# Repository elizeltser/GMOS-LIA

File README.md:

# GMOS Testing Setup

This project is the setup code for GMOS testing setup, used for controlling both STM32 evaluation board and ATI to test and sample GMOS gas sensor device using a two-layer lock-in amplifier setup.

## Code Structure

```
GMOS-LIA/
├── src/
│   ├── stm32/          # STM32 evaluation board code
│   ├── ati/            # ATI control module
│   └── lia/            # Lock-in amplifier implementation
├── tests/              # Test suite
├── examples/           # Usage examples
└── README.md
```

## Running Examples

### Prerequisites
- STM32 development environment
- Python 3.8+
- Required dependencies (see requirements.txt)

### Basic Example

```bash
# Install dependencies
pip install -r requirements.txt

# Run example test
python examples/basic_test.py

# Run sensor sampling
python examples/sample_sensor.py
```

### Testing

```bash
# Run all tests
pytest tests/

# Run specific test module
pytest tests/test_lia.py -v
```

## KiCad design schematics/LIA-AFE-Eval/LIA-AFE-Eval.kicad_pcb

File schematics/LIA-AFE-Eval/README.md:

# LIA-AFE-Eval (KiCad project)

Analog front-end evaluation board for the GMOS lock-in readout. It carries only the analog chain (and possibly the bias DACs), is built to be comfortable to use on the lab bench, and is used to debug the analog chain before the production board [LIA-Readout](../LIA-Readout/README.md). The tested circuits are later integrated into LIA-Readout.

| Path | Contents |
|------|----------|
| `LIA-AFE-Eval.kicad_pro`, `*.kicad_sch` | KiCad project and schematic sheets (schematic rev 0.1 entered, layout not started) |
| `../device_libraries/` | Symbol and footprint libraries shared by all boards |
| `docs/` | Design documentation: start with [docs/README.md](docs/README.md) (document map), then `requirements.md` |
| [../tools/](../tools/README.md) | Shared netlist query and check tools; this board's expected results are in [../tools/checks/LIA-AFE-Eval/](../tools/checks/LIA-AFE-Eval/README.md) |
| [../CLAUDE.md](../CLAUDE.md) | Working rules for Claude Code, shared by all schematic projects |

## Sheets

| Page | Sheet name | File | Contents |
|------|------------|------|----------|
| 1 | (root) | `LIA-AFE-Eval.kicad_sch` | Sheet symbols and inter-sheet wiring |
| 2 | Power | `POWER.kicad_sch` | ±15 V (J4) and ±5 V (J5) bench inputs, reverse-polarity diodes, +5VA, −5VA, +5VP through 1 Ω (E-12) |
| 3 | Connectors | `CONNECTORS.kicad_sch` | NUCLEO control header (IF-5), X/Y SMA and header (IF-3), test loops, mounting holes |
| 4 | DAC | `DAC.kicad_sch` | DAC80508 bias DAC (AN-6) |
| 5 | Excitation | `EXCITATION.kicad_sch` | Gate excitation drive |
| 6 | Sensor | `SENSOR.kicad_sch` | GMOS socket, pixel selection, drain bias, drain test loops, heaters |
| 7 | Front_End | `FRONT_END.kicad_sch` | In-amp and band-pass filter |
| 8 | Demod | `DEMODULATOR.kicad_sch` | Synchronous demodulators and post-filters, X and Y channels on one TMUX6136 (E-13) |

The sheets were entered from [docs/requirements.md](docs/requirements.md) rev B and [docs/component_selection.md](docs/component_selection.md) on 2026-10-29 (check file `../tools/checks/LIA-AFE-Eval/T01.txt`). Pins are connected by short wire stubs with labels; inter-sheet signals use hierarchical labels, rails use global power symbols. Shared circuits keep the LIA-Readout designators and net names; new parts start at R58, C52, U23, D9, J7, TP1. Simulations of the front end are in [`simulations/`](../../simulations/README.md).

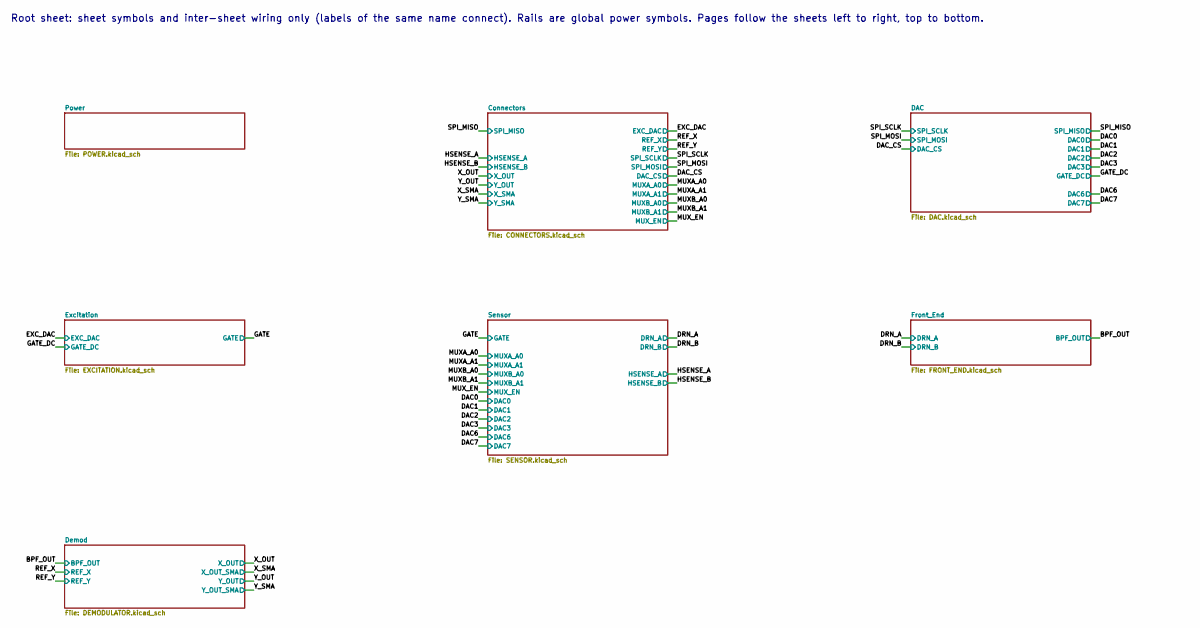
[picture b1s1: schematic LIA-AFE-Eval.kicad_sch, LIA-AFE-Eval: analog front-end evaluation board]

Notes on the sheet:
Root sheet: sheet symbols and inter-sheet wiring only (labels of the same name connect). Rails are global power symbols. Pages follow the sheets left to right, top to bottom.

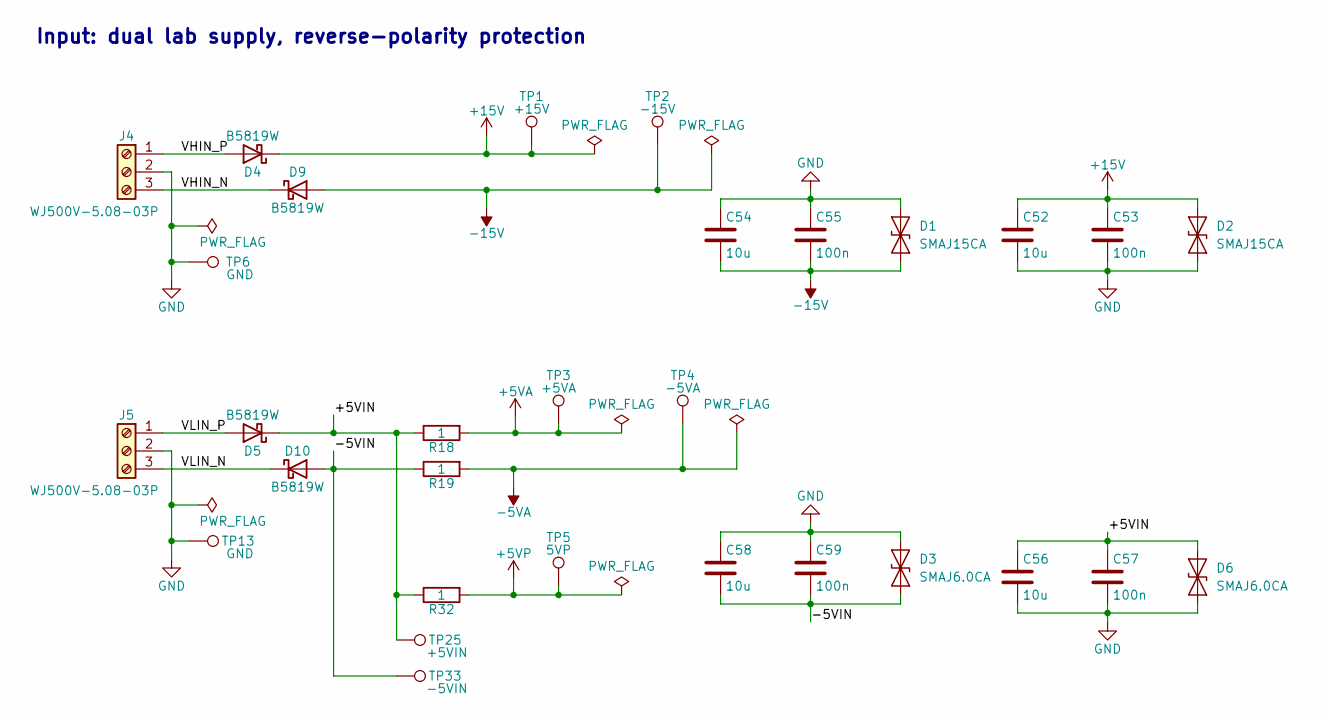
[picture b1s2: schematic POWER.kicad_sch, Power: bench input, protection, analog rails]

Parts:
C52, C54, C56, C58: 10u; C_1206_3216Metric; Voltage 25V
C53, C55, C57, C59: 100n; C_0603_1608Metric
D1, D2: SMAJ15CA; D_SMA
D3, D6: SMAJ6.0CA; D_SMA
D4, D5, D9, D10: B5819W; D_SOD-123; MPN B5819W; LCSC C64885
J4, J5: WJ500V-5.08-03P; TerminalBlock_Phoenix_MKDS-1,5-3-5.08_1x03_P5.08mm_Horizont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; MPN WJ500V-5.08-03P; LCSC C72334
R18, R19, R32: 1; R_0603_1608Metric; Tolerance 0.1%; MPN PTFR0603B1K00N9; LCSC C394536
TP1: +15V; TestPoint_Keystone_5000-5004_Miniature; MPN Keystone 5000; LCSC C5199900
TP2: -15V; TestPoint_Keystone_5000-5004_Miniature; MPN Keystone 5000; LCSC C5199900
TP3: +5VA; TestPoint_Keystone_5000-5004_Miniature; MPN Keystone 5000; LCSC C5199900
TP4: -5VA; TestPoint_Keystone_5000-5004_Miniature; MPN Keystone 5000; LCSC C5199900
TP5: 5VP; TestPoint_Keystone_5000-5004_Miniature; MPN Keystone 5000; LCSC C5199900
TP6, TP13: GND; TestPoint_Keystone_5000-5004_Miniature; MPN Keystone 5001; LCSC C238122
TP25: +5VIN; TestPoint_Keystone_5000-5004_Miniature; MPN Keystone 5001; LCSC C238122
TP33: -5VIN; TestPoint_Keystone_5000-5004_Miniature; MPN Keystone 5001; LCSC C238122

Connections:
+5VA: R18.2, TP3.1 (1_1); also elsewhere on the board
+5VP: R32.2, TP5.1 (1_1); also elsewhere on the board
+15V: C52.1, C53.1, D2.2 (A2), D4.1 (K), TP1.1 (1_1); also elsewhere on the board
-5VA: R19.2, TP4.1 (1_1); also elsewhere on the board
-15V: C54.2, C55.2, D1.1 (A1), D9.2 (A), TP2.1 (1_1); also elsewhere on the board
/Power/+5VIN: C56.1, C57.1, D5.1 (K), D6.2 (A2), R18.1, R32.1, TP25.1 (1_1)
/Power/-5VIN: C58.2, C59.2, D3.1 (A1), D10.2 (A), R19.1, TP33.1 (1_1)
/Power/VHIN_N: D9.1 (K), J4.3
/Power/VHIN_P: D4.2 (A), J4.1
/Power/VLIN_N: D10.1 (K), J5.3
/Power/VLIN_P: D5.2 (A), J5.1
GND: C52.2, C53.2, C54.1, C55.1, C56.2, C57.2, C58.1, C59.1, D1.2 (A2), D2.1 (A1), D3.2 (A2), D6.1 (A1), J4.2, J5.2, TP6.1, TP13.1 (1_1); also elsewhere on the board

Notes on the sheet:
Input: dual lab supply, reverse-polarity protection

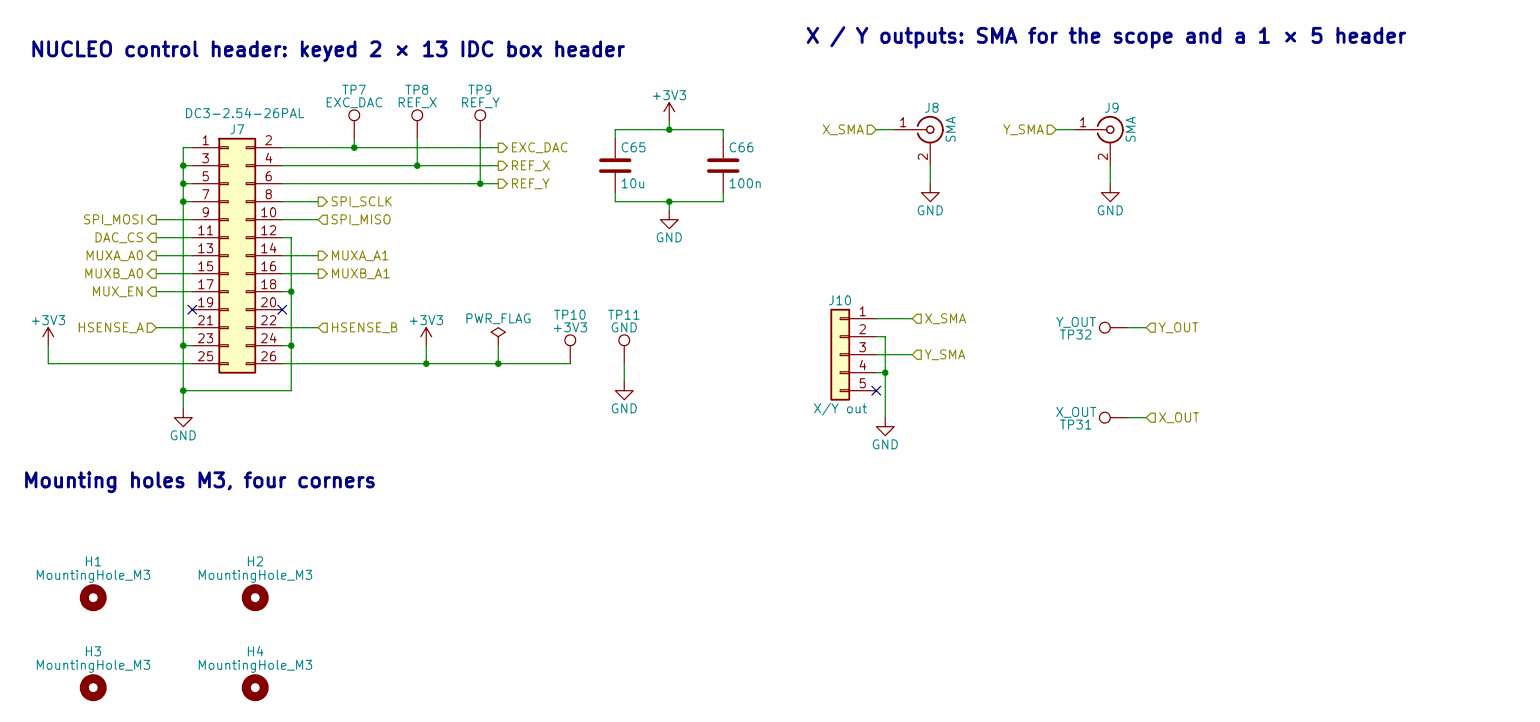
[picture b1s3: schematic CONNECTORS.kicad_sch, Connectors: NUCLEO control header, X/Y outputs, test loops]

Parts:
C65: 10u; C_0805_2012Metric
C66: 100n; C_0603_1608Metric
H1, H2, H3, H4: MountingHole_M3; MountingHole_3.2mm_M3
J7: DC3-2.54-26PAL; IDC-Header_2x13_P2.54mm_Horizontal; MPN DC3-2.54-26PAL; LCSC C5156669
J8, J9: SMA; SMA_Amphenol_132134_Vertical; MPN BWSMA-KE-Z001; LCSC C496549
J10: X/Y out; PinHeader_1x05_P2.54mm_Vertical
TP7: EXC_DAC; TestPoint_Keystone_5000-5004_Miniature; MPN Keystone 5000; LCSC C5199900
TP8: REF_X; TestPoint_Keystone_5000-5004_Miniature; MPN Keystone 5000; LCSC C5199900
TP9: REF_Y; TestPoint_Keystone_5000-5004_Miniature; MPN Keystone 5000; LCSC C5199900
TP10: +3V3; TestPoint_Keystone_5000-5004_Miniature; MPN Keystone 5000; LCSC C5199900
TP11: GND; TestPoint_Keystone_5000-5004_Miniature; MPN Keystone 5001; LCSC C238122
TP31: X_OUT; TestPoint_Keystone_5000-5004_Miniature; MPN Keystone 5000; LCSC C5199900
TP32: Y_OUT; TestPoint_Keystone_5000-5004_Miniature; MPN Keystone 5000; LCSC C5199900

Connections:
+3V3: C65.1, C66.1, J7.25, J7.26, TP10.1 (1_1); also elsewhere on the board
/DAC_CS: J7.11; also elsewhere on the board
/EXC_DAC: J7.2, TP7.1 (1_1); also elsewhere on the board
/HSENSE_A: J7.21; also elsewhere on the board
/HSENSE_B: J7.22; also elsewhere on the board
/MUXA_A0: J7.13; also elsewhere on the board
/MUXA_A1: J7.14; also elsewhere on the board
/MUXB_A0: J7.15; also elsewhere on the board
/MUXB_A1: J7.16; also elsewhere on the board
/MUX_EN: J7.17; also elsewhere on the board
/REF_X: J7.4, TP8.1 (1_1); also elsewhere on the board
/REF_Y: J7.6, TP9.1 (1_1); also elsewhere on the board
/SPI_MISO: J7.10; also elsewhere on the board
/SPI_MOSI: J7.9; also elsewhere on the board
/SPI_SCLK: J7.8; also elsewhere on the board
/X_OUT: TP31.1 (1_1); also elsewhere on the board
/X_SMA: J8.1 (In), J10.1; also elsewhere on the board
/Y_OUT: TP32.1 (1_1); also elsewhere on the board
/Y_SMA: J9.1 (In), J10.3; also elsewhere on the board
GND: C65.2, C66.2, J7.1, J7.3, J7.5, J7.7, J7.12, J7.18, J7.23, J7.24, J8.2 (Ext), J9.2 (Ext), J10.2, J10.4, TP11.1 (1_1); also elsewhere on the board

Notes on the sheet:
Mounting holes M3, four corners
X / Y outputs: SMA for the scope and a 1 × 5 header
NUCLEO control header: keyed 2 × 13 IDC box header

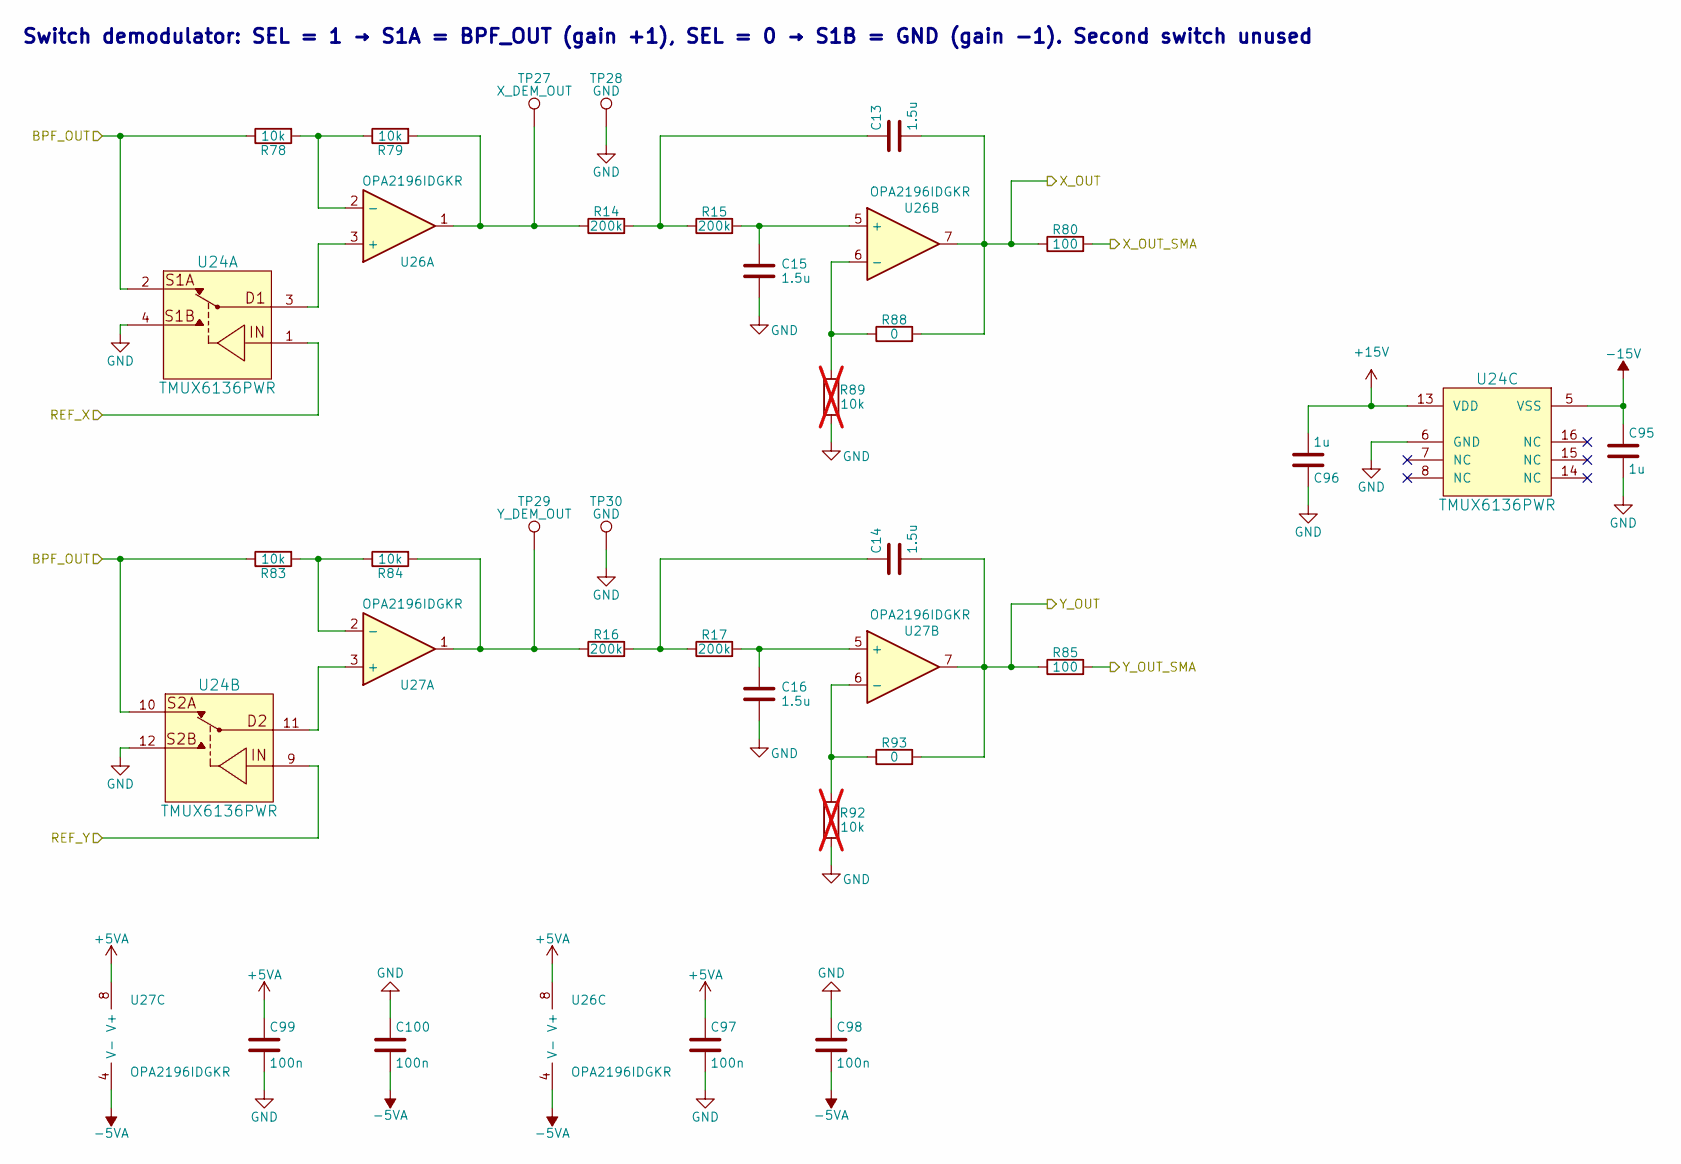
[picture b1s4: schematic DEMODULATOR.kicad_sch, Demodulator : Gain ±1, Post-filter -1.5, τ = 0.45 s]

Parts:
C13, C14, C15, C16: 1.5u; C_1206_3216Metric; Tolerance 20%; MPN 16MU155MA23216; LCSC C3776792
C95, C96: 1u; C_0603_1608Metric; Voltage 25V
C97, C98, C99, C100: 100n; C_0603_1608Metric
R14, R15, R16, R17: 200k; R_0603_1608Metric; Tolerance 0.1%; MPN RT0603BRD07200KL; LCSC C728585
R78, R79, R83, R84: 10k; R_0603_1608Metric; Tolerance 0.1%; MPN PTFR0603B10K0N9; LCSC C394535
R80, R85: 100; R_0603_1608Metric
R88, R93: 0; R_0603_1608Metric
R89, R92: 10k; R_0603_1608Metric; not fitted
TP27: X_DEM_OUT; TestPoint_Keystone_5000-5004_Miniature; MPN Keystone 5000; LCSC C5199900
TP28, TP30: GND; TestPoint_Keystone_5000-5004_Miniature; MPN Keystone 5001; LCSC C238122
TP29: Y_DEM_OUT; TestPoint_Keystone_5000-5004_Miniature; MPN Keystone 5000; LCSC C5199900
U24: TMUX6136PWR; TSSOP-16_4.4x5mm_P0.65mm; MPN TMUX6136PWR; LCSC C2673380
U26, U27: OPA2196IDGKR; VSSOP-8_3x3mm_P0.65mm; MPN OPA2196IDGKR; LCSC C2057920

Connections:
+5VA: C97.1, C99.1, U26.8 (V+), U27.8 (V+); also elsewhere on the board
+15V: C96.2, U24.13 (VDD); also elsewhere on the board
-5VA: C98.2, C100.2, U26.4 (V-), U27.4 (V-); also elsewhere on the board
-15V: C95.1, U24.5 (VSS); also elsewhere on the board
/BPF_OUT: R78.1, R83.1, U24.2 (S1A), U24.10 (S2A); also elsewhere on the board
/REF_X: U24.1 (SEL1); also elsewhere on the board
/REF_Y: U24.9 (SEL2); also elsewhere on the board
/X_OUT: C13.2, R80.1, R88.2, U26.7; also elsewhere on the board
/X_SMA: R80.2; also elsewhere on the board
/Y_OUT: C14.2, R85.1, R93.2, U27.7; also elsewhere on the board
/Y_SMA: R85.2; also elsewhere on the board
GND: C15.2, C16.2, C95.2, C96.1, C97.2, C98.1, C99.2, C100.1, R89.2, R92.2, TP28.1 (1_1), TP30.1 (1_1), U24.4 (S1B), U24.6 (GND), U24.12 (S2B); also elsewhere on the board
unnamed: C13.1, R14.2, R15.1
unnamed: C14.1, R16.2, R17.1
unnamed: R14.1, R79.2, TP27.1 (1_1), U26.1
unnamed: R16.1, R84.2, TP29.1 (1_1), U27.1
unnamed: U24.3 (D1), U26.3 (+)
unnamed: U24.11 (D2), U27.3 (+)
unnamed: R78.2, R79.1, U26.2 (-)
unnamed: C15.1, R15.2, U26.5 (+)
unnamed: R88.1, R89.1, U26.6 (-)
unnamed: R83.2, R84.1, U27.2 (-)
unnamed: C16.1, R17.2, U27.5 (+)
unnamed: R92.1, R93.1, U27.6 (-)

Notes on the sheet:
Switch demodulator: SEL = 1 → S1A = BPF_OUT (gain +1), SEL = 0 → S1B = GND (gain -1). Second switch unused

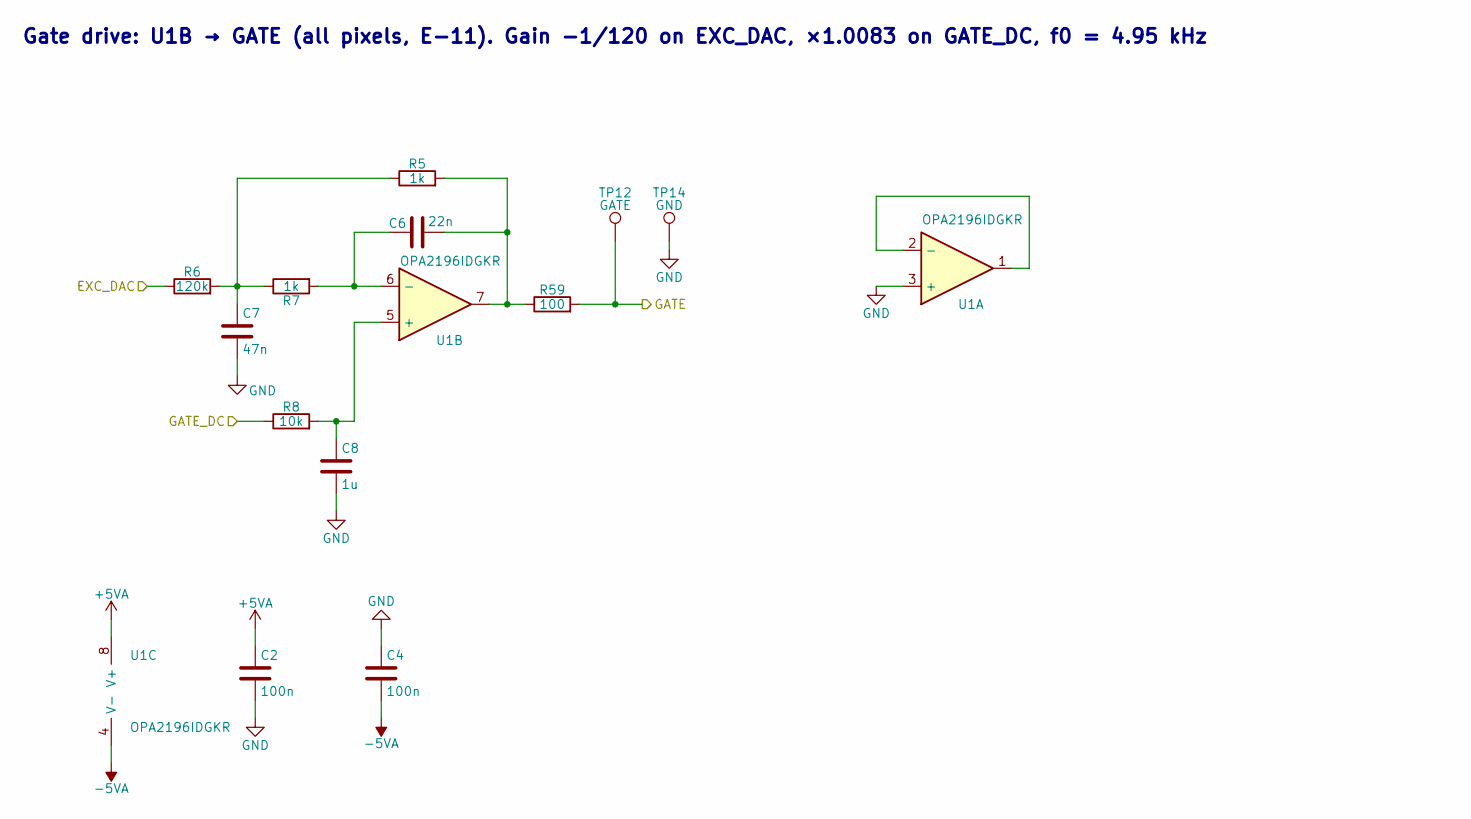
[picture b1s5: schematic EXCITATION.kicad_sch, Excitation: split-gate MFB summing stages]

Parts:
C2, C4: 100n; C_0603_1608Metric
C6: 22n; C_0805_2012Metric; Tolerance 5%; MPN GRM21B5C1H223JA01L; LCSC C77069
C7: 47n; C_1206_3216Metric; Tolerance 5%; MPN GRM31M5C1H473JA01L; LCSC C21812
C8: 1u; C_0603_1608Metric
R5, R7: 1k; R_0603_1608Metric; Tolerance 0.1%; MPN PTFR0603B1K00N9; LCSC C394536
R6: 120k; R_0603_1608Metric; Tolerance 0.1%; MPN RT0603BRD07120KL; LCSC C705720
R8: 10k; R_0603_1608Metric
R59: 100; R_0603_1608Metric
TP12: GATE; TestPoint_Keystone_5000-5004_Miniature; MPN Keystone 5000; LCSC C5199900
TP14: GND; TestPoint_Keystone_5000-5004_Miniature; MPN Keystone 5001; LCSC C238122
U1: OPA2196IDGKR; VSSOP-8_3x3mm_P0.65mm; MPN OPA2196IDGKR; LCSC C2057920

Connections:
+5VA: C2.1, U1.8 (V+); also elsewhere on the board
-5VA: C4.2, U1.4 (V-); also elsewhere on the board
/EXC_DAC: R6.1; also elsewhere on the board
/GATE: R59.2, TP12.1 (1_1); also elsewhere on the board
/GATE_DC: R8.1; also elsewhere on the board
GND: C2.2, C4.1, C7.2, C8.2, TP14.1 (1_1), U1.3 (+); also elsewhere on the board
unnamed: C6.2, R5.2, R59.1, U1.7
unnamed: C7.1, R5.1, R6.2, R7.1
unnamed: U1.1, U1.2 (-)
unnamed: C8.1, R8.2, U1.5 (+)
unnamed: C6.1, R7.2, U1.6 (-)

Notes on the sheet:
Gate drive: U1B → GATE (all pixels, E-11). Gain -1/120 on EXC_DAC, ×1.0083 on GATE_DC, f0 = 4.95 kHz

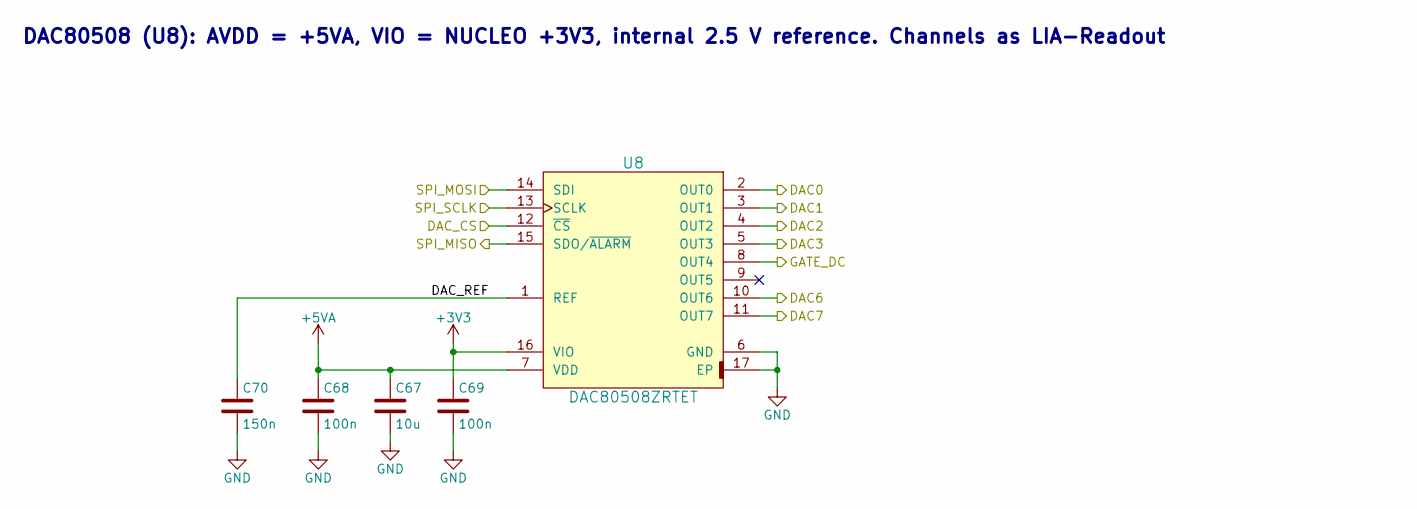
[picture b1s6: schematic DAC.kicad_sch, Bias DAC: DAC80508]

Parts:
C67: 10u; C_0805_2012Metric
C68, C69: 100n; C_0603_1608Metric
C70: 150n; C_0603_1608Metric
U8: DAC80508ZRTET; WQFN-16-1EP_3x3mm_P0.5mm_EP1.68x1.68mm; MPN DAC80508ZRTET; LCSC C2863226

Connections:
+3V3: C69.1, U8.16 (VIO); also elsewhere on the board
+5VA: C67.1, C68.1, U8.7 (VDD); also elsewhere on the board
/DAC0: U8.2 (OUT0); also elsewhere on the board
/DAC1: U8.3 (OUT1); also elsewhere on the board
/DAC2: U8.4 (OUT2); also elsewhere on the board
/DAC3: U8.5 (OUT3); also elsewhere on the board
/DAC6: U8.10 (OUT6); also elsewhere on the board
/DAC7: U8.11 (OUT7); also elsewhere on the board
/DAC/DAC_REF: C70.1, U8.1 (REF)
/DAC_CS: U8.12 (~CS); also elsewhere on the board
/GATE_DC: U8.8 (OUT4); also elsewhere on the board
/SPI_MISO: U8.15 (SDO/~ALARM); also elsewhere on the board
/SPI_MOSI: U8.14 (SDI); also elsewhere on the board
/SPI_SCLK: U8.13 (SCLK); also elsewhere on the board
GND: C67.2, C68.2, C69.2, C70.2, U8.6 (GND), U8.17 (EP); also elsewhere on the board

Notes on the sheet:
DAC80508 (U8): AVDD = +5VA, VIO = NUCLEO +3V3, internal 2.5 V reference. Channels as LIA-Readout

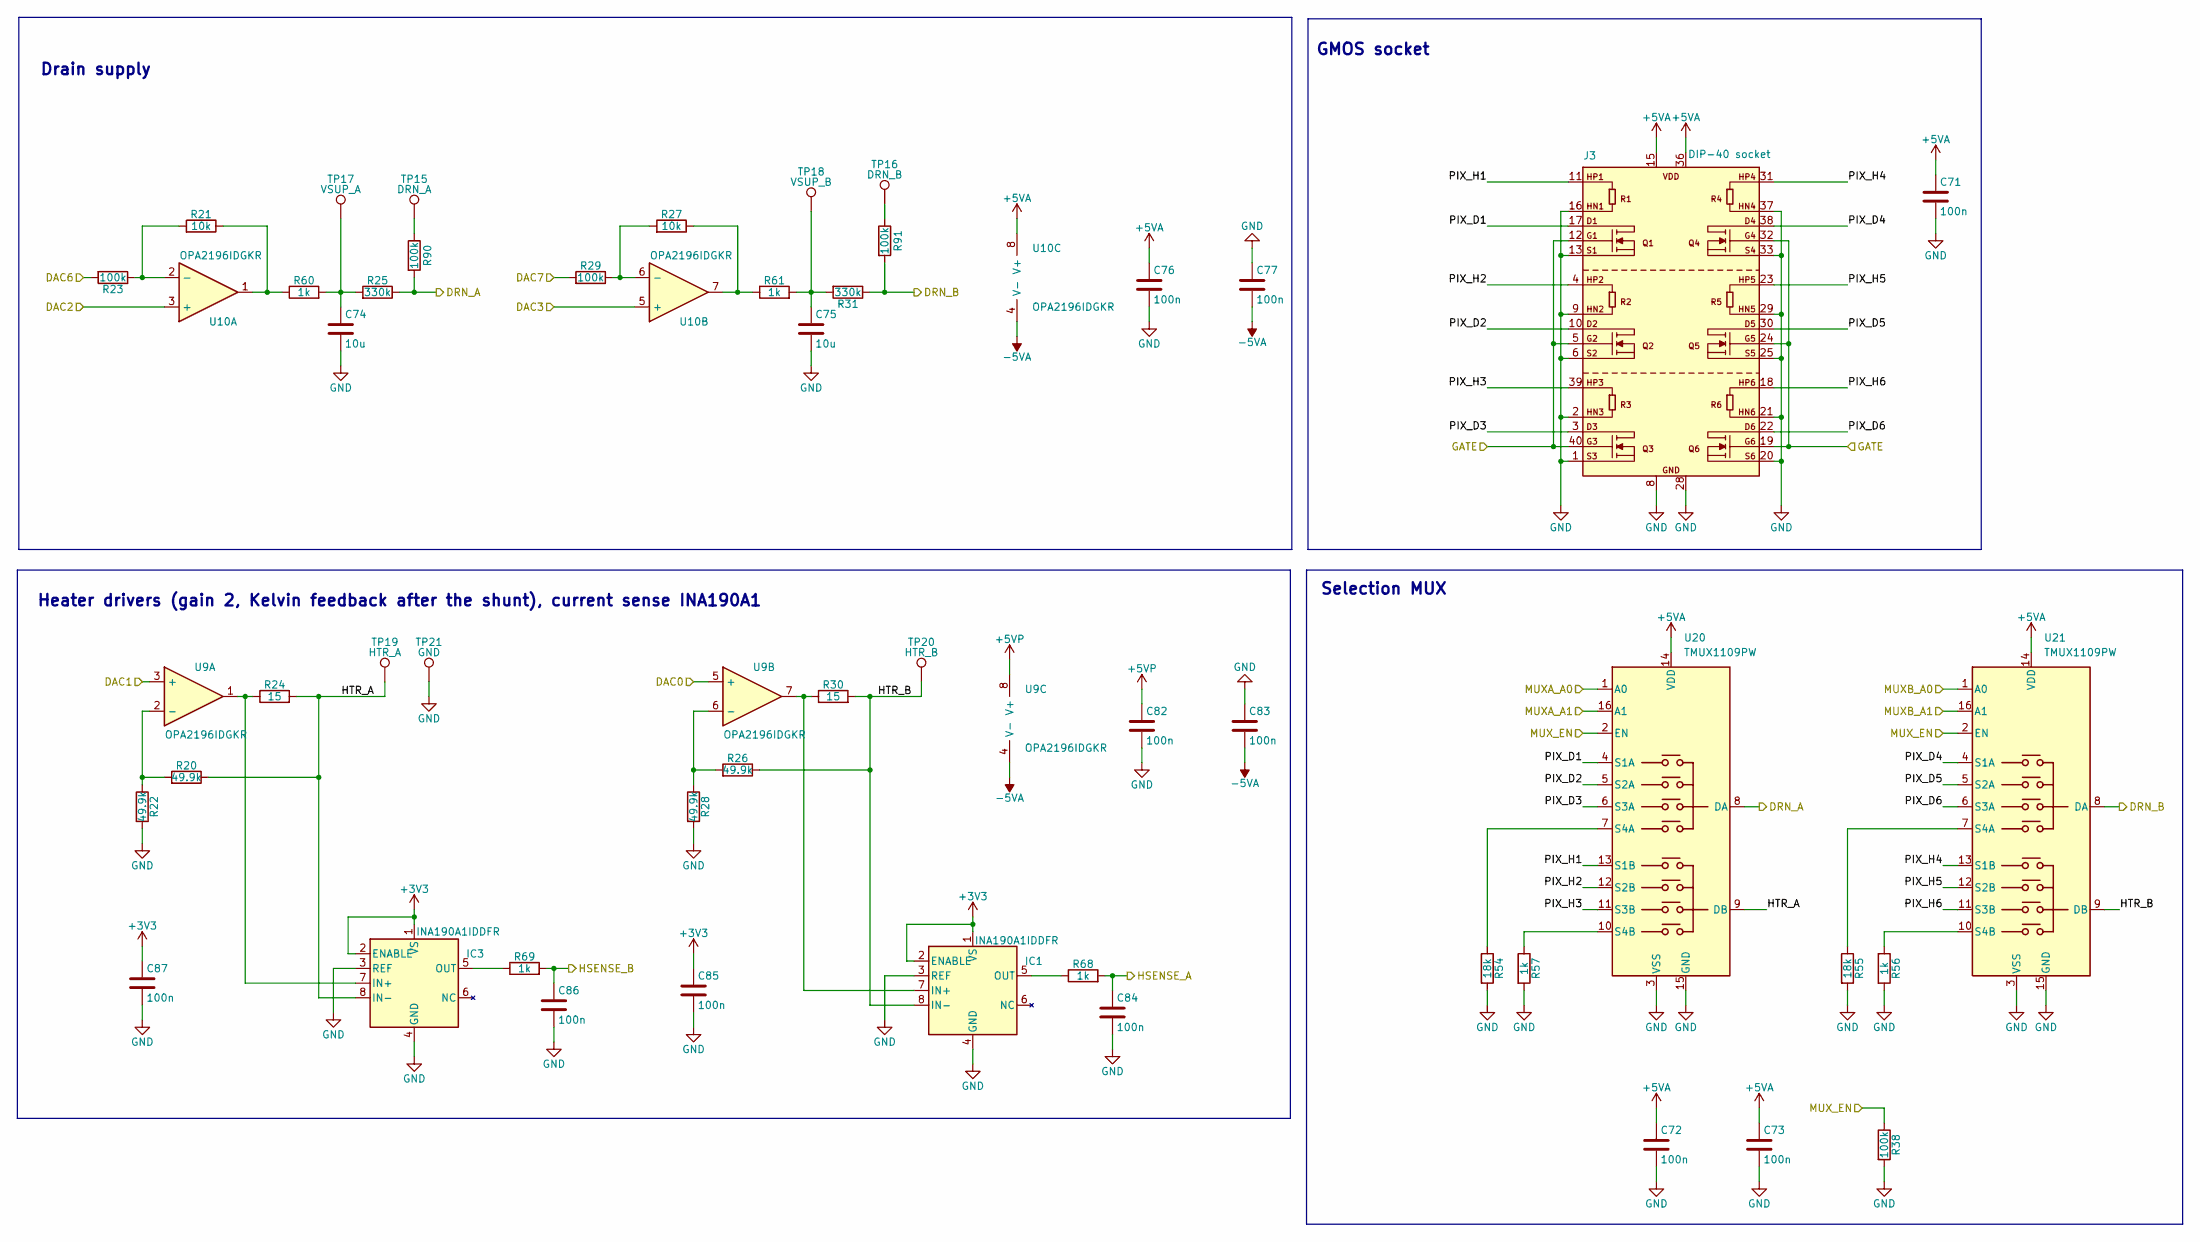
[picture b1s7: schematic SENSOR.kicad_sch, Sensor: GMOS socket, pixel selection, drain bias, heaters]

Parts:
C71, C72, C73, C76, C77, C82, C83, C84, C85, C86, C87: 100n; C_0603_1608Metric
C74, C75: 10u; C_0805_2012Metric
IC1, IC3: INA190A1IDDFR; TSOT-23-8; MPN INA190A1IDDFR; LCSC C1852068
J3: DIP-40 socket; DIP-40_W15.24mm; MPN DIP-40 socket 15.24 mm; LCSC C2332
R20, R22, R26, R28: 49.9k; R_0603_1608Metric; Tolerance 0.1%; MPN RT0603BRD0749K9L; LCSC C705780
R21, R27: 10k; R_0603_1608Metric; Tolerance 0.1%; MPN PTFR0603B10K0N9; LCSC C394535
R23, R29, R90, R91: 100k; R_0603_1608Metric; Tolerance 0.1%; MPN PTFR0603B100KN9; LCSC C394537
R24, R30: 15; R_0603_1608Metric; Tolerance 0.1%; MPN RT0603BRD0715RL; LCSC C705727
R25, R31: 330k; R_0603_1608Metric; Tolerance 0.1%; MPN RT0603BRB07330KL; LCSC C860332
R38: 100k; R_0603_1608Metric
R54, R55: 18k; R_0603_1608Metric; Tolerance 0.1%; MPN PTFR0603B18K0N9; LCSC C2692864
R56, R57: 1k; R_0805_2012Metric; Tolerance 0.1%; MPN RT0805BRD071KL; LCSC C110774
R60, R61: 1k; R_0603_1608Metric; Tolerance 0.1%; MPN PTFR0603B1K00N9; LCSC C394536
R68, R69: 1k; R_0603_1608Metric
TP15: DRN_A; TestPoint_Keystone_5000-5004_Miniature; MPN Keystone 5000; LCSC C5199900
TP16: DRN_B; TestPoint_Keystone_5000-5004_Miniature; MPN Keystone 5000; LCSC C5199900
TP17: VSUP_A; TestPoint_Keystone_5000-5004_Miniature; MPN Keystone 5000; LCSC C5199900
TP18: VSUP_B; TestPoint_Keystone_5000-5004_Miniature; MPN Keystone 5000; LCSC C5199900
TP19: HTR_A; TestPoint_Keystone_5000-5004_Miniature; MPN Keystone 5000; LCSC C5199900
TP20: HTR_B; TestPoint_Keystone_5000-5004_Miniature; MPN Keystone 5000; LCSC C5199900
TP21: GND; TestPoint_Keystone_5000-5004_Miniature; MPN Keystone 5001; LCSC C238122
U9, U10: OPA2196IDGKR; VSSOP-8_3x3mm_P0.65mm; MPN OPA2196IDGKR; LCSC C2057920
U20, U21: TMUX1109PW; TSSOP-16_4.4x5mm_P0.65mm; MPN TMUX1109PWR

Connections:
+3V3: C85.1, C87.1, IC1.1 (VS), IC1.2 (ENABLE), IC3.1 (VS), IC3.2 (ENABLE); also elsewhere on the board
+5VA: C71.1, C72.1, C73.1, C76.1, J3.15 (VDD), J3.36 (VDD), U10.8 (V+), U20.14 (VDD), U21.14 (VDD); also elsewhere on the board
+5VP: C82.1, U9.8 (V+); also elsewhere on the board
-5VA: C77.2, C83.2, U9.4 (V-), U10.4 (V-); also elsewhere on the board
/DAC0: U9.5 (+); also elsewhere on the board
/DAC1: U9.3 (+); also elsewhere on the board
/DAC2: U10.3 (+); also elsewhere on the board
/DAC3: U10.5 (+); also elsewhere on the board
/DAC6: R23.2; also elsewhere on the board
/DAC7: R29.2; also elsewhere on the board
/DRN_A: R25.1, R90.2, U20.8 (DA); also elsewhere on the board
/DRN_B: R31.1, R91.2, U21.8 (DA); also elsewhere on the board
/GATE: J3.5 (G2), J3.12 (G1), J3.19 (G6), J3.24 (G5), J3.32 (G4), J3.40 (G3); also elsewhere on the board
/HSENSE_A: C84.1, R68.2; also elsewhere on the board
/HSENSE_B: C86.1, R69.2; also elsewhere on the board
/MUXA_A0: U20.1 (A0); also elsewhere on the board
/MUXA_A1: U20.16 (A1); also elsewhere on the board
/MUXB_A0: U21.1 (A0); also elsewhere on the board
/MUXB_A1: U21.16 (A1); also elsewhere on the board
/MUX_EN: R38.1, U20.2 (EN), U21.2 (EN); also elsewhere on the board
/Sensor/HTR_A: IC3.8 (IN-), R20.1, R24.2, TP19.1 (1_1), U20.9 (DB)
/Sensor/HTR_B: IC1.8 (IN-), R26.1, R30.2, TP20.1 (1_1), U21.9 (DB)
/Sensor/PIX_D1: J3.17 (D1), U20.4 (S1A)
/Sensor/PIX_D2: J3.10 (D2), U20.5 (S2A)
/Sensor/PIX_D3: J3.3 (D3), U20.6 (S3A)
/Sensor/PIX_D4: J3.38 (D4), U21.4 (S1A)
/Sensor/PIX_D5: J3.30 (D5), U21.5 (S2A)
/Sensor/PIX_D6: J3.22 (D6), U21.6 (S3A)
/Sensor/PIX_H1: J3.11 (HP1), U20.13 (S1B)
/Sensor/PIX_H2: J3.4 (HP2), U20.12 (S2B)
/Sensor/PIX_H3: J3.39 (HP3), U20.11 (S3B)
/Sensor/PIX_H4: J3.31 (HP4), U21.13 (S1B)
/Sensor/PIX_H5: J3.23 (HP5), U21.12 (S2B)
/Sensor/PIX_H6: J3.18 (HP6), U21.11 (S3B)
GND: C71.2, C72.2, C73.2, C74.2, C75.2, C76.2, C77.1, C82.2, C83.1, C84.2, C85.2, C86.2, C87.2, IC1.3 (REF), IC1.4 (GND), IC3.3 (REF), IC3.4 (GND), J3.1 (S3), J3.2 (HN3), J3.6 (S2), J3.8 (GND), J3.9 (HN2), J3.13 (S1), J3.16 (HN1), J3.20 (S6), J3.21 (HN6), J3.25 (S5), J3.28 (GND), J3.29 (HN5), J3.33 (S4), J3.37 (HN4), R22.2, R28.2, R38.2, R54.2, R55.2, R56.2, R57.2, TP21.1 (1_1), U20.3 (VSS), U20.15 (GND), U21.3 (VSS), U21.15 (GND); also elsewhere on the board
unnamed: C74.1, R25.2, R60.2, TP17.1 (1_1)
unnamed: C75.1, R31.2, R61.2, TP18.1 (1_1)
unnamed: IC1.7 (IN+), R30.1, U9.7
unnamed: IC1.5 (OUT), R68.1
unnamed: IC3.7 (IN+), R24.1, U9.1
unnamed: IC3.5 (OUT), R69.1
unnamed: R21.1, R60.1, U10.1
unnamed: R27.1, R61.1, U10.7
unnamed: R90.1, TP15.1 (1_1)
unnamed: R91.1, TP16.1 (1_1)
unnamed: R20.2, R22.1, U9.2 (-)
unnamed: R26.2, R28.1, U9.6 (-)
unnamed: R21.2, R23.1, U10.2 (-)
unnamed: R27.2, R29.1, U10.6 (-)
unnamed: R54.1, U20.7 (S4A)
unnamed: R57.1, U20.10 (S4B)
unnamed: R55.1, U21.7 (S4A)
unnamed: R56.1, U21.10 (S4B)

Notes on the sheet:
Heater drivers (gain 2, Kelvin feedback after the shunt), current sense INA190A1
Drain supply
Selection MUX
GMOS socket

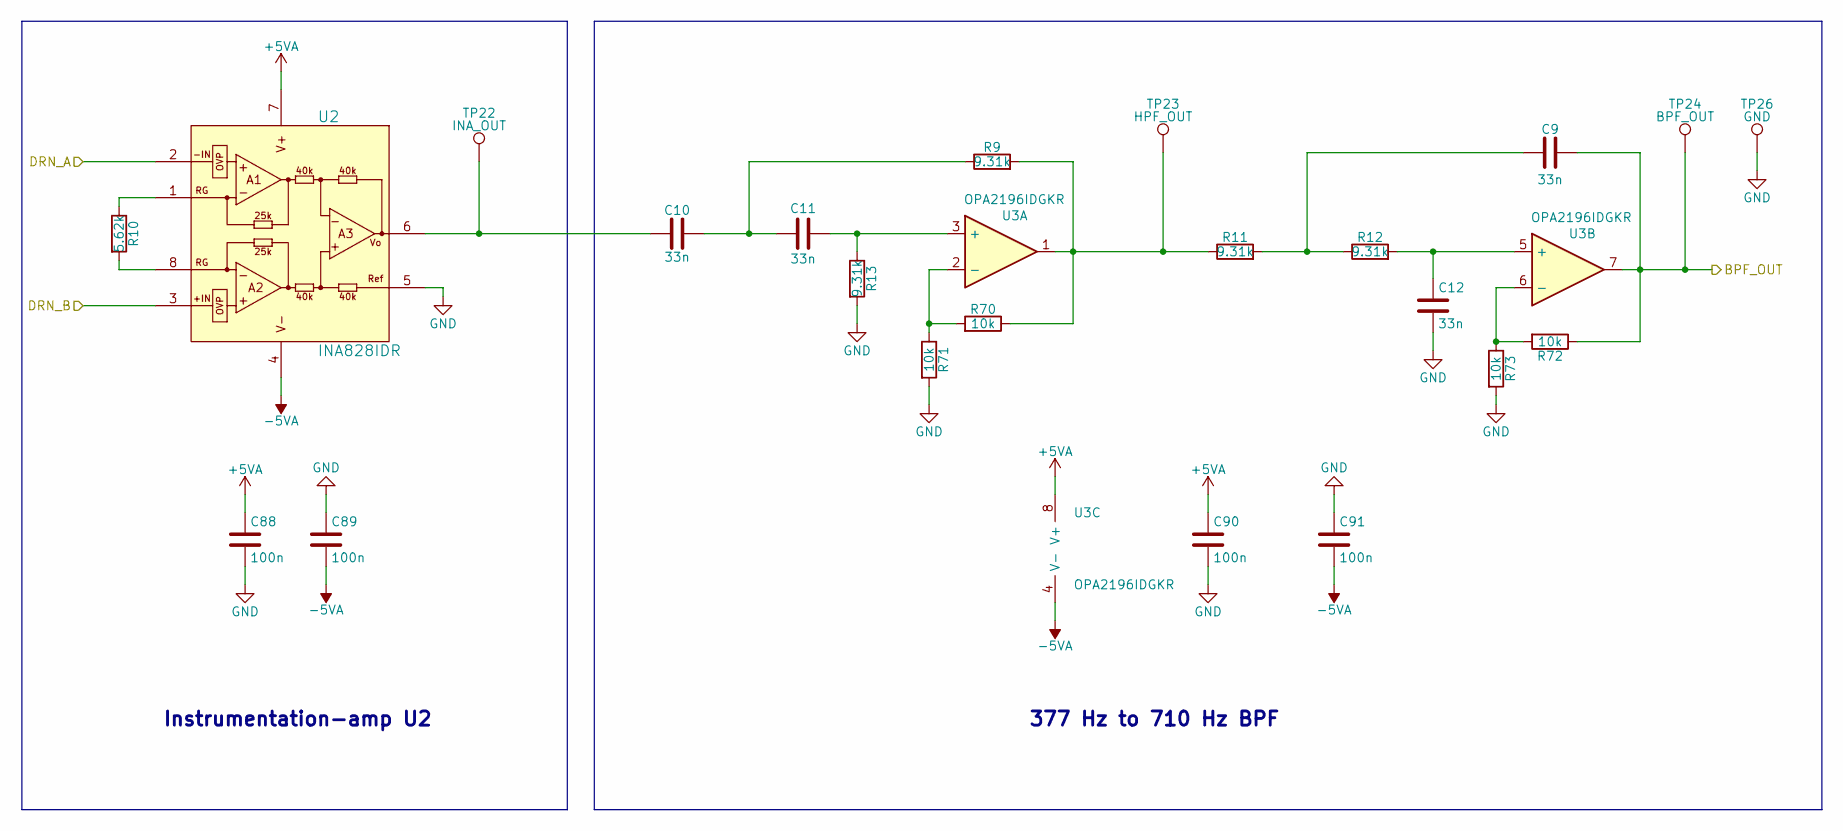
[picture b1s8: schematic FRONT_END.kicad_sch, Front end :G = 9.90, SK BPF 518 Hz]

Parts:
C9, C10, C11, C12: 33n; C_0805_2012Metric; Tolerance 5%; MPN C2012C0G1H333JT000N; LCSC C76628
C88, C89, C90, C91: 100n; C_0603_1608Metric
R9, R11, R12, R13: 9.31k; R_0603_1608Metric; Tolerance 0.1%; MPN ARG03BTC9311; LCSC C2686441
R10: 5.62k; R_0603_1608Metric; Tolerance 0.1%; MPN RT0603BRD075K62L; LCSC C705789
R70, R71, R72, R73: 10k; R_0603_1608Metric; Tolerance 0.1%; MPN PTFR0603B10K0N9; LCSC C394535
TP22: INA_OUT; TestPoint_Keystone_5000-5004_Miniature; MPN Keystone 5000; LCSC C5199900
TP23: HPF_OUT; TestPoint_Keystone_5000-5004_Miniature; MPN Keystone 5000; LCSC C5199900
TP24: BPF_OUT; TestPoint_Keystone_5000-5004_Miniature; MPN Keystone 5000; LCSC C5199900
TP26: GND; TestPoint_Keystone_5000-5004_Miniature; MPN Keystone 5001; LCSC C238122
U2: INA828IDR; SOIC-8_3.9x4.9mm_P1.27mm; MPN INA828IDR; LCSC C544342
U3: OPA2196IDGKR; VSSOP-8_3x3mm_P0.65mm; MPN OPA2196IDGKR; LCSC C2057920

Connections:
+5VA: C88.1, C90.1, U2.7 (V+), U3.8 (V+); also elsewhere on the board
-5VA: C89.2, C91.2, U2.4 (V-), U3.4 (V-); also elsewhere on the board
/BPF_OUT: C9.2, R72.1, TP24.1 (1_1), U3.7; also elsewhere on the board
/DRN_A: U2.2 (VIN-); also elsewhere on the board
/DRN_B: U2.3 (VIN+); also elsewhere on the board
GND: C12.2, C88.2, C89.1, C90.2, C91.1, R13.2, R71.2, R73.2, TP26.1 (1_1), U2.5 (REF); also elsewhere on the board
unnamed: C9.1, R11.2, R12.1
unnamed: C10.2, C11.1, R9.1
unnamed: R10.1, U2.1 (RG)
unnamed: R10.2, U2.8 (RG)
unnamed: R9.2, R11.1, R70.1, TP23.1 (1_1), U3.1
unnamed: C10.1, TP22.1 (1_1), U2.6 (VO)
unnamed: C11.2, R13.1, U3.3 (+)
unnamed: R70.2, R71.1, U3.2 (-)
unnamed: C12.1, R12.2, U3.5 (+)
unnamed: R72.2, R73.1, U3.6 (-)

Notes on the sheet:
377 Hz to 710 Hz BPF
Instrumentation-amp U2

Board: 4 copper layers, 168 parts (13 on the bottom side), 102 nets, no tracks yet.

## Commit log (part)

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2025-07-14 Updated TreeTTester and more
2025-07-19 Major update on LIASetup
2025-07-19 fixed VITester - now passes basic tests
2025-07-22 not sure what changed but OK
2025-07-23 changes from lab
2025-12-25 extensive cleanup
2025-12-27 Major cleanup, upload of STM project
2025-12-27 now it can also flash the mcu
2026-01-07 MCP changes, running well
2026-02-19 save changes - then redo all
2026-02-21 Redo of many things - now FSD centered
2026-03-07 Implement most of the tests - not tested yet
2026-04-05 This is a commit for adding "readout.tex" and its compilation to the repository for specific file Yeal required.
2026-04-11 moved to thesis folder name, intro grows larger, claude.md splitted
2026-04-22 matching transistors page
2026-04-24 lia tests for optimization of phase
